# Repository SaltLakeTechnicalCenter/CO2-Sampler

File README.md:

# Introduction
This device uses an infrared gas sensor from [Dynament](https://www.dynament.com/gas-types/carbon-dioxide/) to monitor the concentration of carbon dioxide in the air.  When threshold conditions are met an [Entech Micro-QT valve](https://www.entechinst.com/product-category/micro-qt-valves/) on an evacuated chamber is open allowing a sample of the air to be captured.  This is accomplished by pressing a tube into the valve with a SG90 servo motor connected to a cam.  A [LilyGO TTGO T2 development board](https://www.amazon.com/TTGO-T2-Bluetooth-Development-Module/dp/B07B6MS253) communicates with the sensor (via [RS232](https://www.dynament.com/_webedit/uploaded-files/All%20Files/SIL%20Data/tds0045_1.44.pdf)) and logs data to a microSD card.  A simple user interface is accomplished with the onboard button and OLED display. More advanced features will be accessable through an Android device paired to the onboard bluetooth.

# Pinout
| GPIO |  Device |            Notes           |
|------|---------|----------------------------|
|   0  |         | outputs PWM signal at boot |
|   1  |  Serial |      serial monitor TX     |
|   2  |   RFID  |         Dynament RX        |
|   3  |  Serial |      serial monitor RX     |
|   4  |   OLED  |             RST            |
|   5  | SD card |             CS             |
| 6    | SPI     | SPI flash                  |
| 7    | SPI     | SPI flash                  |
| 8    | SPI     | SPI flash                  |
| 9    | SPI     | SPI flash                  |
| 10   | SPI     | SPI flash                  |
| 11   | SPI     | SPI flash                  |
| 12   |         | boot fail if pulled high   |
| 13   | OLED    | MOSI/SDA                   |
| 14   | OLED    | SCLK/SCL                   |
| 15   | OLED    | CS                         |
| 16   | OLED    | DC                         |
| 17   | RFID    | Dynament TX                |
| 18   | SD card | CLK                        |
| 19   | SD card | DO MISO                    |
| 21   | BMP180  | SDA                        |
| 22   | BMP180  | SCL                        |
| 23   | SD card | CMP/MOSI                   |
| 25   |         |                            |
| 26   |         |                            |
| 27   | Buzzer  | Buzzer                     |
| 32   | Servo   | Servo                      |
| 33   |         |                            |
| 34   | RFID    | Analog                     |
| 35   | Battery | Battery                    |
| 36   | Button  | Button                     |
| 39   |         | Inaccessible               |

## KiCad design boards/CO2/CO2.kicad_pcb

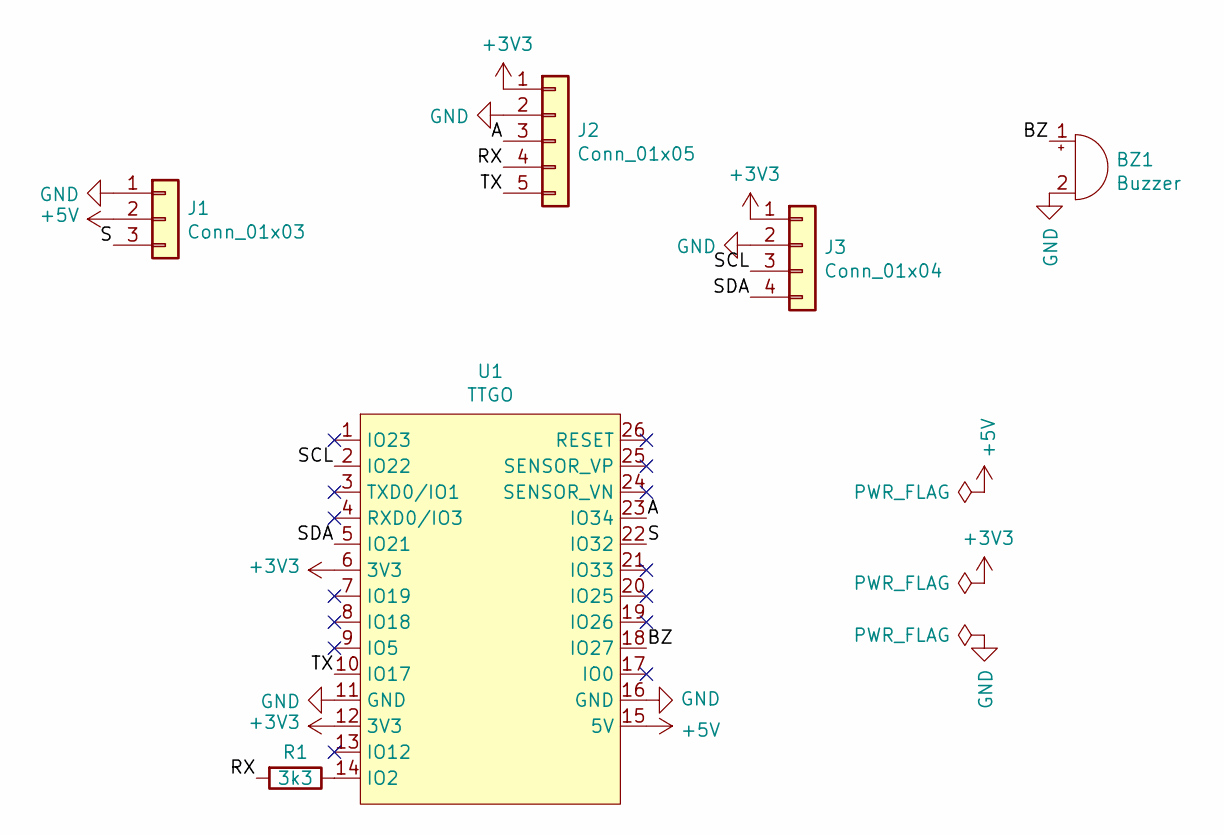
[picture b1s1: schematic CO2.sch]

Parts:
BZ1: Buzzer; Buzzer_12x9.5RM7.6
J1: Conn_01x03; PinHeader_1x03_P2.54mm_Horizontal
J2: Conn_01x05; JST_XH_S5B-XH-A_1x05_P2.50mm_Horizontal
J3: Conn_01x04; PinHeader_1x04_P2.54mm_Vertical
R1: 3k3; R_Axial_DIN0204_L3.6mm_D1.6mm_P7.62mm_Horizontal
U1: TTGO

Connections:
+3V3: J2.1, J3.1, U1.6 (3V3), U1.12 (3V3)
+5V: J1.2, U1.15 (5V)
/A: J2.3, U1.23 (IO34)
/BZ: BZ1.1 (-), U1.18 (IO27)
/RX: J2.4, R1.2
/S: J1.3, U1.22 (IO32)
/SCL: J3.3, U1.2 (IO22)
/SDA: J3.4, U1.5 (IO21)
/TX: J2.5, U1.10 (IO17)
GND: BZ1.2 (+), J1.1, J2.2, J3.2, U1.11 (GND), U1.16 (GND)
unnamed: R1.1, U1.14 (IO2)

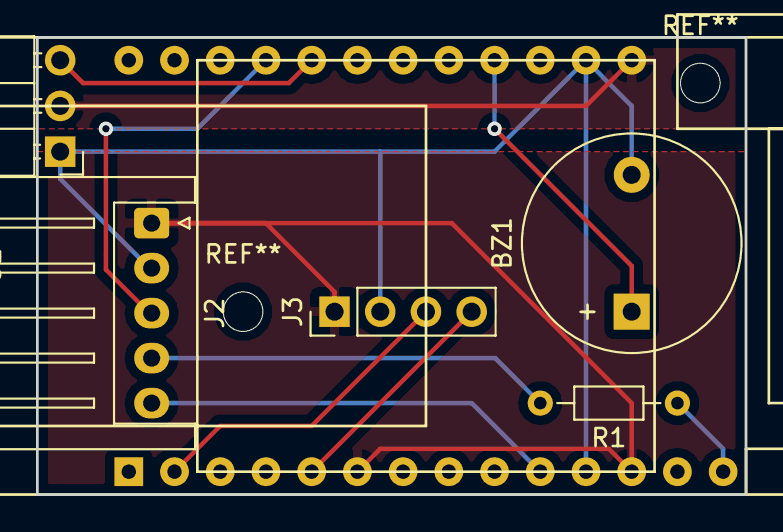
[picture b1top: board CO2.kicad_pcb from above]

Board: 2 copper layers, 39.4 x 25.4 mm, 6 parts (0 on the bottom side), 11 nets.

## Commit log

2019-10-08 Uploaded Firmware
2019-10-08 Uploaded circuit boards
    I used KiCad to design these boards.
2019-12-04 Added link to tds0045 document from Dynament.
